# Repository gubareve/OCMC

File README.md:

# Open-source Custom Mechanical Keyboard

OCMC is a custom PCB running on the ATMEGA328P chipset.
Designed using KiCAD 6.0 and assembled using JLCPCB.

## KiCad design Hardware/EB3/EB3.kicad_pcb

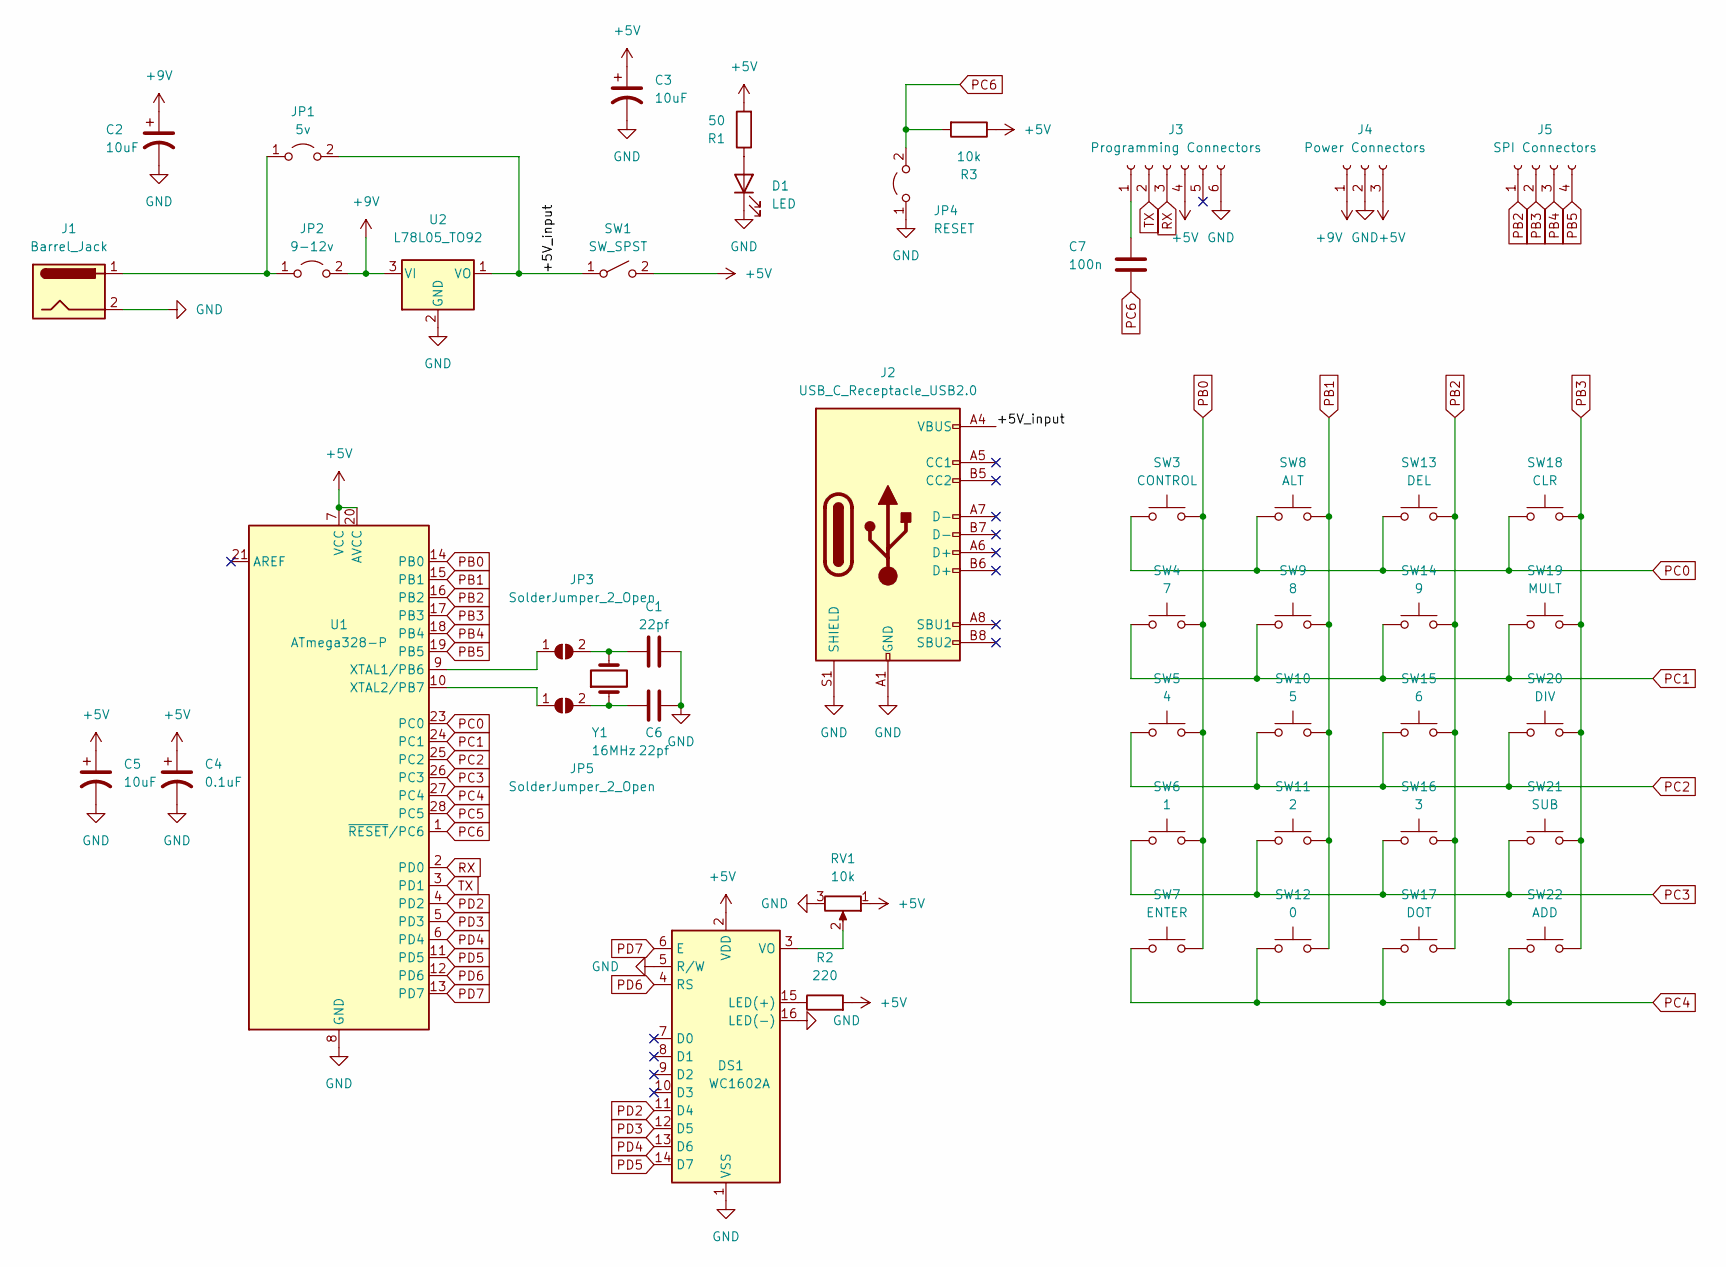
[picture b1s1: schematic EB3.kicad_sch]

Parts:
C1, C6: 22pf; C_0805_2012Metric; LCSC C1804
C2, C3, C5: 10uF; C_0805_2012Metric; LCSC C17024
C4: 0.1uF; C_0805_2012Metric; LCSC C49678
C7: 100n; C_0805_2012Metric; LCSC C49678
D1: LED; LED_0805_2012Metric; LCSC C84256
DS1: WC1602A
J1: Barrel_Jack; BarrelJack_GCT_DCJ200-10-A_Horizontal
J2: USB_C_Receptacle_USB2.0
J3: Programming Connectors; PinSocket_1x06_P2.54mm_Vertical
J4: Power Connectors; PinSocket_1x03_P2.54mm_Vertical
J5: SPI Connectors; PinSocket_1x04_P2.54mm_Vertical
JP1: 5v; TestPoint_2Pads_Pitch2.54mm_Drill0.8mm
JP2: 9-12v; TestPoint_2Pads_Pitch2.54mm_Drill0.8mm
JP3, JP5: SolderJumper_2_Open; SolderJumper-2_P1.3mm_Open_RoundedPad1.0x1.5mm
JP4: RESET; TestPoint_2Pads_Pitch2.54mm_Drill0.8mm
R1: 50; R_0805_2012Metric; LCSC C23182
R2: 220; R_0805_2012Metric; LCSC C17520
R3: 10k; R_0805_2012Metric; LCSC C17414
RV1: 10k; Potentiometer_Piher_PT-6-V_Vertical_Hole
SW1: SW_SPST; SW_Push_2P2T_Toggle_CK_PVA2OAH5xxxxxxV2
SW3: CONTROL; SW_Cherry_MX_Plate_1.00u
SW4: 7; SW_Cherry_MX_Plate_1.00u
SW5: 4; SW_Cherry_MX_Plate_1.00u
SW6: 1; SW_Cherry_MX_Plate_1.00u
SW7: ENTER; SW_Cherry_MX_Plate_1.00u
SW8: ALT; SW_Cherry_MX_Plate_1.00u
SW9: 8; SW_Cherry_MX_Plate_1.00u
SW10: 5; SW_Cherry_MX_Plate_1.00u
SW11: 2; SW_Cherry_MX_Plate_1.00u
SW12: 0; SW_Cherry_MX_Plate_1.00u
SW13: DEL; SW_Cherry_MX_Plate_1.00u
SW14: 9; SW_Cherry_MX_Plate_1.00u
SW15: 6; SW_Cherry_MX_Plate_1.00u
SW16: 3; SW_Cherry_MX_Plate_1.00u
SW17: DOT; SW_Cherry_MX_Plate_1.00u
SW18: CLR; SW_Cherry_MX_Plate_1.00u
SW19: MULT; SW_Cherry_MX_Plate_1.00u
SW20: DIV; SW_Cherry_MX_Plate_1.00u
SW21: SUB; SW_Cherry_MX_Plate_1.00u
SW22: ADD; SW_Cherry_MX_Plate_1.00u
U1: ATmega328-P; DIP-28_W7.62mm
U2: L78L05_TO92; TO-92_Inline
Y1: 16MHz; Crystal_SMD_3225-4Pin_3.2x2.5mm; LCSC C13738

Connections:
+5V: C3.1, C4.1, C5.1, DS1.2 (VDD), J3.4, J4.3, R1.2, R2.2, R3.1, RV1.1, SW1.2 (B), U1.7 (VCC), U1.20 (AVCC)
+9V: C2.1, J4.1, JP2.2 (B), U2.3 (VI)
/+5V_input: J2.A4 (VBUS), J2.A9 (VBUS), J2.B4 (VBUS), J2.B9 (VBUS), JP1.2 (B), SW1.1 (A), U2.1 (VO)
GND: C1.2, C2.2, C3.2, C4.2, C5.2, C6.2, D1.1 (K), DS1.1 (VSS), DS1.5 (R/W), DS1.16 (LED(-)), J1.2, J2.A1 (GND), J2.A12 (GND), J2.B1 (GND), J2.B12 (GND), J2.S1 (SHIELD), J3.6, J4.2, JP4.1 (A), RV1.3, U1.8 (GND), U1.22 (GND), U2.2 (GND), Y1.3
unnamed: C1.1, JP3.2 (B), Y1.2
unnamed: C6.1, JP5.2 (B), Y1.1
unnamed: C7.1, J3.1
unnamed: D1.2 (A), R1.1
unnamed: DS1.3 (VO), RV1.2
unnamed: DS1.15 (LED(+)), R2.1
unnamed: J1.1, JP1.1 (A), JP2.1 (A)
unnamed: JP3.1 (A), U1.9 (XTAL1/PB6)
unnamed: JP5.1 (A), U1.10 (XTAL2/PB7)
PB0: SW3.2, SW4.2, SW5.2, SW6.2, SW7.2, U1.14 (PB0)
PB1: SW8.2, SW9.2, SW10.2, SW11.2, SW12.2, U1.15 (PB1)
PB2: J5.1, SW13.2, SW14.2, SW15.2, SW16.2, SW17.2, U1.16 (PB2)
PB3: J5.2, SW18.2, SW19.2, SW20.2, SW21.2, SW22.2, U1.17 (PB3)
PB4: J5.3, U1.18 (PB4)
PB5: J5.4, U1.19 (PB5)
PC0: SW3.1, SW8.1, SW13.1, SW18.1, U1.23 (PC0)
PC1: SW4.1, SW9.1, SW14.1, SW19.1, U1.24 (PC1)
PC2: SW5.1, SW10.1, SW15.1, SW20.1, U1.25 (PC2)
PC3: SW6.1, SW11.1, SW16.1, SW21.1, U1.26 (PC3)
PC4: SW7.1, SW12.1, SW17.1, SW22.1, U1.27 (PC4)
PC5: U1.28 (PC5)
PC6: C7.2, JP4.2 (B), R3.2, U1.1 (~RESET/PC6)
PD2: DS1.11 (D4), U1.4 (PD2)
PD3: DS1.12 (D5), U1.5 (PD3)
PD4: DS1.13 (D6), U1.6 (PD4)
PD5: DS1.14 (D7), U1.11 (PD5)
PD6: DS1.4 (RS), U1.12 (PD6)
PD7: DS1.6 (E), U1.13 (PD7)
RX: J3.3, U1.2 (PD0)
TX: J3.2, U1.3 (PD1)

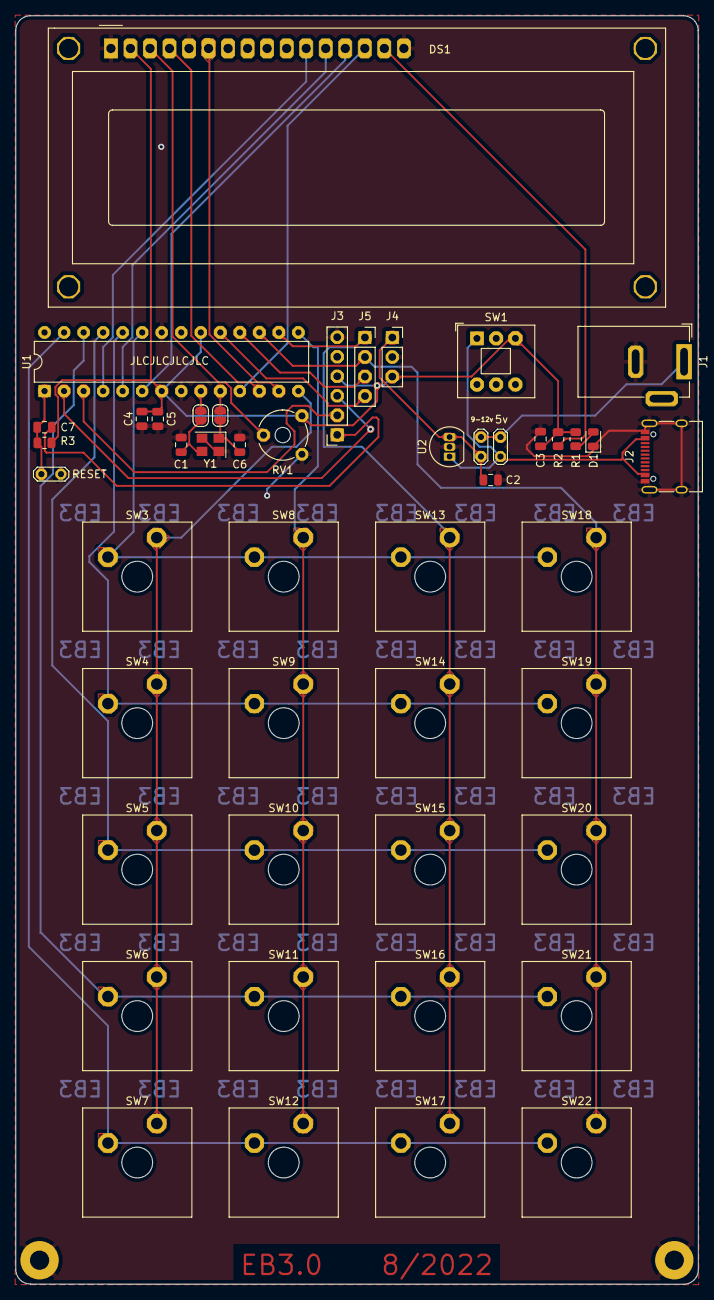
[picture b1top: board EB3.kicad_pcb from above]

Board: 2 copper layers, 88.8 x 165.0 mm, 47 parts (0 on the bottom side), 33 nets.

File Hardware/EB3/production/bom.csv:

Designator,Footprint,Quantity,Value,LCSC Part #
J2,USB_C_Receptacle_XKB_U262-16XN-4BVC11,1,USB_C_Receptacle,
Y1,Crystal_SMD_3225-4Pin_3.2x2.5mm,1,16MHz,C13738
D1,LED_0805_2012Metric,1,LED,C84256
C5,C_0805_2012Metric,1,10uF,C17024
JP3,SolderJumper-2_P1.3mm_Open_RoundedPad1.0x1.5mm,1,SolderJumper_2_Open,
J4,PinSocket_1x03_P2.54mm_Vertical,1,Power Connectors,
J3,PinSocket_1x06_P2.54mm_Vertical,1,Programming Connectors,
C2,C_0805_2012Metric,1,10uF,C17024
DS1,WC1602A,1,WC1602A,
SW3,SW_Cherry_MX_Plate_1.00u,1,CONTROL,
SW15,SW_Cherry_MX_Plate_1.00u,1,6,
SW9,SW_Cherry_MX_Plate_1.00u,1,8,
SW5,SW_Cherry_MX_Plate_1.00u,1,4,
U1,DIP-28_W7.62mm,1,ATmega328-P,
JP5,SolderJumper-2_P1.3mm_Open_RoundedPad1.0x1.5mm,1,SolderJumper_2_Open,
RV1,Potentiometer_Piher_PT-6-V_Vertical_Hole,1,10k,
R3,R_0805_2012Metric,1,10k,C17414
SW10,SW_Cherry_MX_Plate_1.00u,1,5,
SW7,SW_Cherry_MX_Plate_1.00u,1,ENTER,
C3,C_0805_2012Metric,1,10uF,C17024
JP2,TestPoint_2Pads_Pitch2.54mm_Drill0.8mm,1,9-12v,
SW12,SW_Cherry_MX_Plate_1.00u,1,0,
SW19,SW_Cherry_MX_Plate_1.00u,1,MULT,
SW13,SW_Cherry_MX_Plate_1.00u,1,DEL,
JP4,TestPoint_2Pads_Pitch2.54mm_Drill0.8mm,1,RESET,
C4,C_0805_2012Metric,1,0.1uF,C49678
SW21,SW_Cherry_MX_Plate_1.00u,1,SUB,
J1,BarrelJack_GCT_DCJ200-10-A_Horizontal,1,Barrel_Jack,
SW20,SW_Cherry_MX_Plate_1.00u,1,DIV,
SW8,SW_Cherry_MX_Plate_1.00u,1,ALT,
C7,C_0805_2012Metric,1,100n,C49678
C6,C_0805_2012Metric,1,22pf,C1804
SW11,SW_Cherry_MX_Plate_1.00u,1,2,
J5,PinSocket_1x04_P2.54mm_Vertical,1,SPI Connectors,
SW16,SW_Cherry_MX_Plate_1.00u,1,3,
C1,C_0805_2012Metric,1,22pf,C1804
SW18,SW_Cherry_MX_Plate_1.00u,1,CLR,
SW4,SW_Cherry_MX_Plate_1.00u,1,7,
SW6,SW_Cherry_MX_Plate_1.00u,1,1,
SW1,SW_Push_2P2T_Toggle_CK_PVA2OAH5xxxxxxV2,1,SW_SPST,
SW22,SW_Cherry_MX_Plate_1.00u,1,ADD,
R1,R_0805_2012Metric,1,50,
SW17,SW_Cherry_MX_Plate_1.00u,1,DOT,
U2,TO-92_Inline,1,L78L05_TO92,
SW14,SW_Cherry_MX_Plate_1.00u,1,9,
JP1,TestPoint_2Pads_Pitch2.54mm_Drill0.8mm,1,5v,
R2,R_0805_2012Metric,1,220,C17520

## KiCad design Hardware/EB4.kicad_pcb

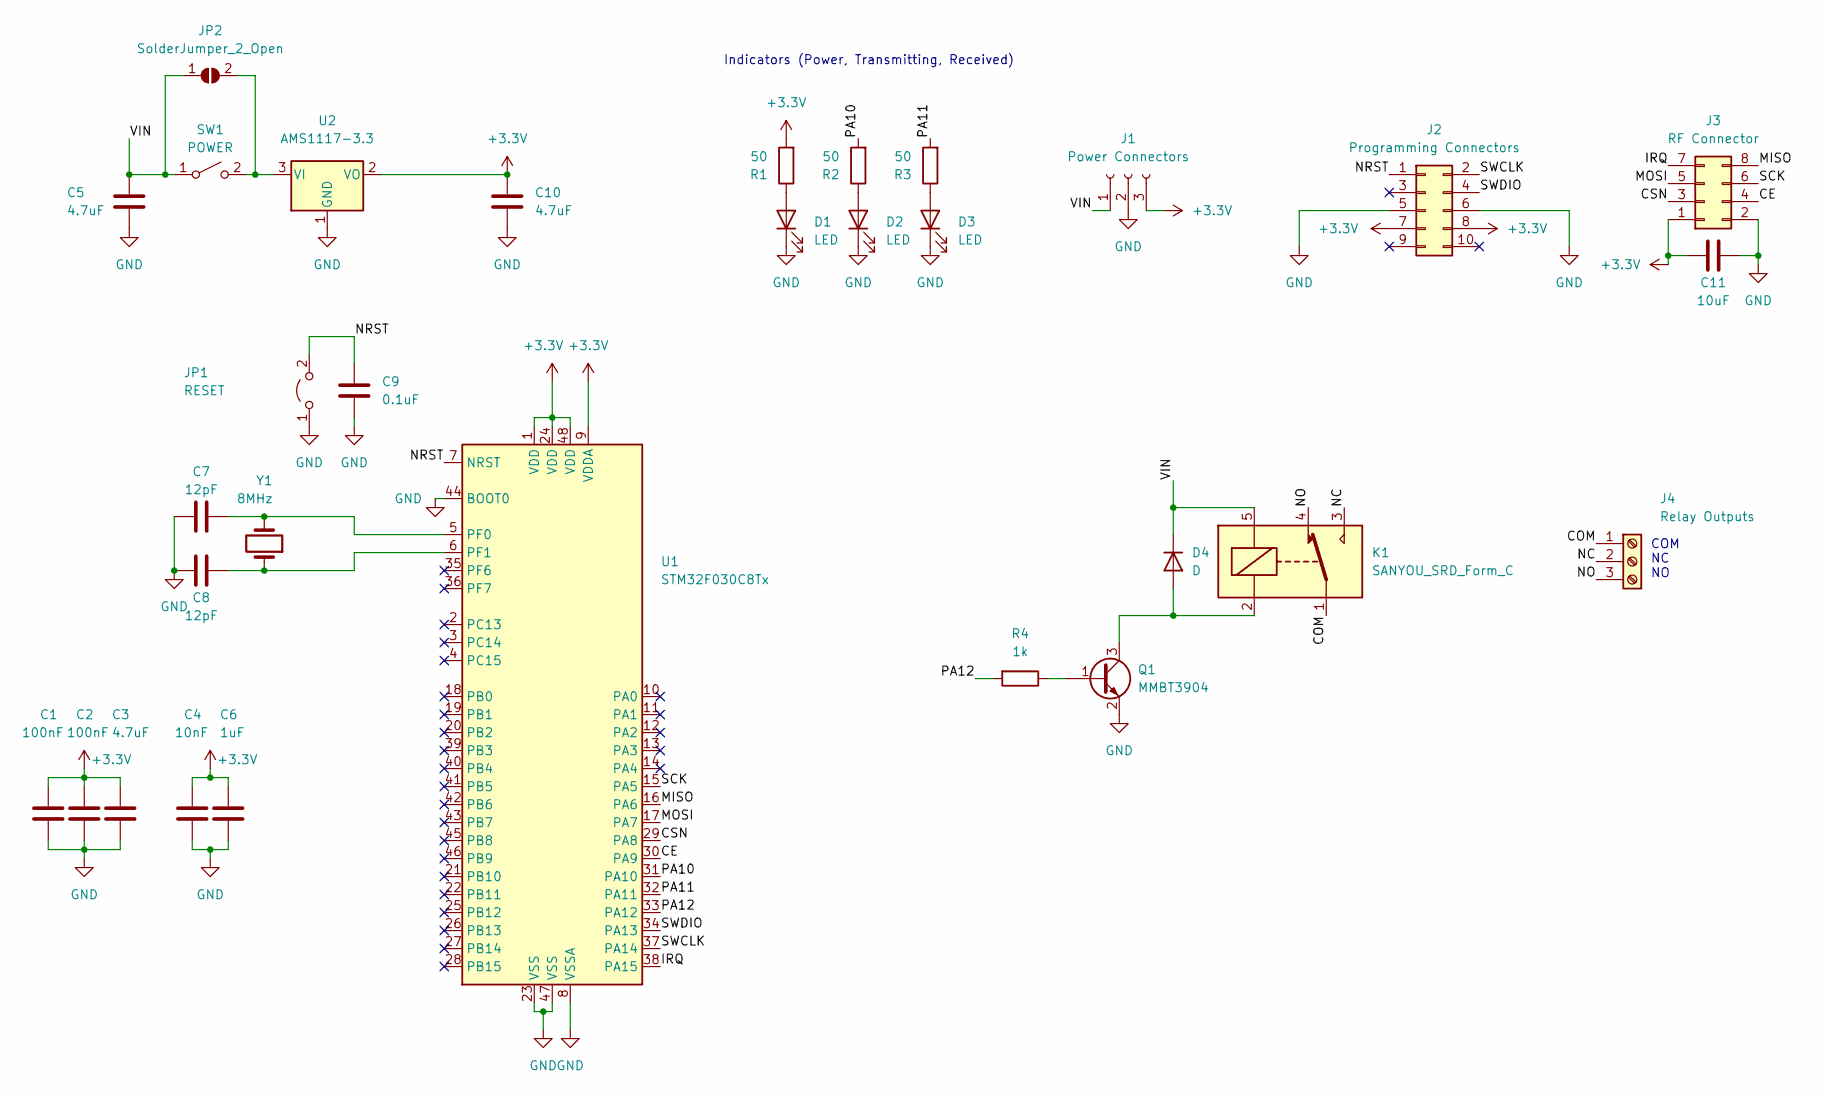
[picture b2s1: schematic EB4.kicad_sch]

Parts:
C1, C2: 100nF; C_0402_1005Metric; LCSC C1525
C3, C5, C10: 4.7uF; C_0402_1005Metric; LCSC C23733
C4: 10nF; C_0402_1005Metric; LCSC C15195
C6: 1uF; C_0402_1005Metric; LCSC C52923
C7, C8: 12pF; C_0402_1005Metric; LCSC C1547
C9: 0.1uF; C_0402_1005Metric; LCSC C1525
C11: 10uF; C_0603_1608Metric; LCSC C19702
D1, D2, D3: LED; LED_0805_2012Metric; LCSC C84256
D4: D; D_SOD-323; LCSC C191023
J1: Power Connectors; PinSocket_1x03_P2.54mm_Vertical
J2: Programming Connectors; PinSocket_2x05_P2.54mm_Vertical
J3: RF Connector; PinSocket_2x04_P2.54mm_Vertical
J4: Relay Outputs; PinSocket_1x03_P2.54mm_Vertical
JP1: RESET; TestPoint_2Pads_Pitch2.54mm_Drill0.8mm
JP2: SolderJumper_2_Open; SolderJumper-2_P1.3mm_Open_TrianglePad1.0x1.5mm
K1: SANYOU_SRD_Form_C; Relay_SPDT_SANYOU_SRD_Series_Form_C
Q1: MMBT3904; SOT-23; LCSC C20526
R1, R2, R3: 50; R_0402_1005Metric; LCSC C25125
R4: 1k; R_0402_1005Metric; LCSC C11702
SW1: POWER; SW_Push_1P1T_NO_CK_KSC6xxJ; LCSC C318884
U1: STM32F030C8Tx; LQFP-48_7x7mm_P0.5mm; LCSC C23922
U2: AMS1117-3.3; SOT-223-3_TabPin2; LCSC C6186
Y1: 8MHz; Crystal_SMD_HC49-SD; LCSC C12674

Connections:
+3.3V: C1.1, C2.1, C3.1, C4.1, C6.1, C10.1, C11.2, J1.3, J2.7, J2.8, J3.1, R1.2, U1.1 (VDD), U1.9 (VDDA), U1.24 (VDD), U1.48 (VDD), U2.2 (VO)
/CE: J3.4, U1.30 (PA9)
/COM: J4.1, K1.1
/CSN: J3.3, U1.29 (PA8)
/IRQ: J3.7, U1.38 (PA15)
/MISO: J3.8, U1.16 (PA6)
/MOSI: J3.5, U1.17 (PA7)
/NC: J4.2, K1.3
/NO: J4.3, K1.4
/NRST: C9.1, J2.1, JP1.2 (B), U1.7 (NRST)
/PA10: R2.2, U1.31 (PA10)
/PA11: R3.2, U1.32 (PA11)
/PA12: R4.2, U1.33 (PA12)
/SCK: J3.6, U1.15 (PA5)
/SWCLK: J2.2, U1.37 (PA14)
/SWDIO: J2.4, U1.34 (PA13)
/VIN: C5.1, D4.1 (K), J1.1, JP2.1 (A), K1.5, SW1.1 (A)
GND: C1.2, C2.2, C3.2, C4.2, C5.2, C6.2, C7.2, C8.2, C9.2, C10.2, C11.1, D1.1 (K), D2.1 (K), D3.1 (K), J1.2, J2.5, J2.6, J3.2, JP1.1 (A), Q1.2 (E), U1.8 (VSSA), U1.23 (VSS), U1.44 (BOOT0), U1.47 (VSS), U2.1 (GND)
unnamed: C7.1, U1.5 (PF0), Y1.2
unnamed: C8.1, U1.6 (PF1), Y1.1
unnamed: D1.2 (A), R1.1
unnamed: D2.2 (A), R2.1
unnamed: D3.2 (A), R3.1
unnamed: D4.2 (A), K1.2, Q1.3 (C)
unnamed: JP2.2 (B), SW1.2 (B), U2.3 (VI)
unnamed: Q1.1 (B), R4.1

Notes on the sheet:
COM NC NO
Indicators (Power, Transmitting, Received)

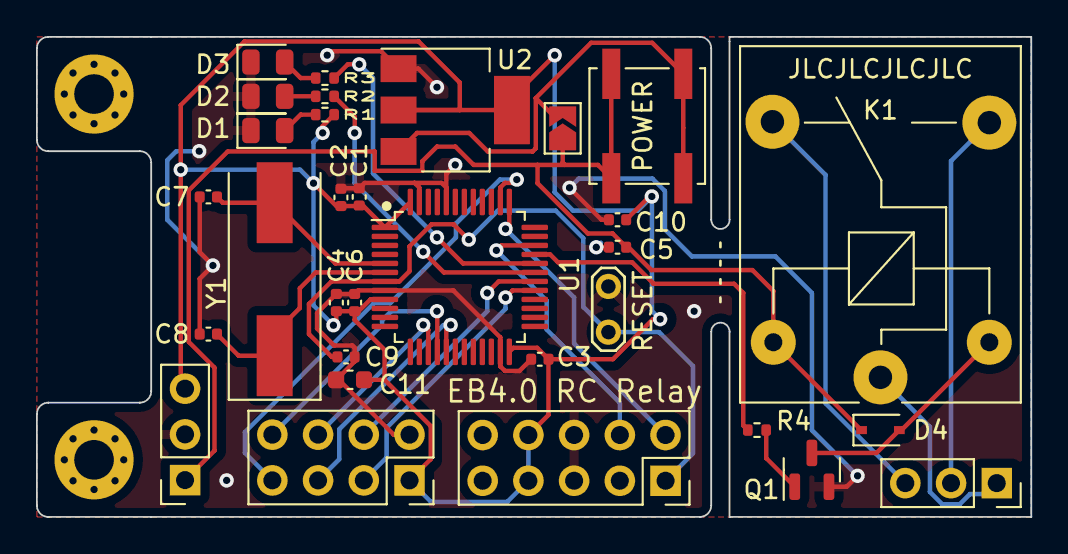
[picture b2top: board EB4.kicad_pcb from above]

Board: 2 copper layers, 55.2 x 26.7 mm, 31 parts (0 on the bottom side), 26 nets.

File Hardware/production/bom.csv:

Designator,Footprint,Quantity,Value,LCSC Part #
D4,D_SOD-323,1,D,C191023
D2,LED_0805_2012Metric,1,LED,C84256
J1,PinSocket_1x03_P2.54mm_Vertical,1,Power Connectors,
C6,C_0402_1005Metric,1,1uF,C52923
U1,LQFP-48_7x7mm_P0.5mm,1,STM32F030C8Tx,C23922
C2,C_0402_1005Metric,1,100nF,C1525
R1,R_0402_1005Metric,1,50,C25125
C10,C_0402_1005Metric,1,4.7uF,C23733
Q1,SOT-23,1,MMBT3904,C20526
C7,C_0402_1005Metric,1,12pF,C1547
C9,C_0402_1005Metric,1,0.1uF,C1525
C8,C_0402_1005Metric,1,12pF,C1547
JP2,SolderJumper-2_P1.3mm_Open_TrianglePad1.0x1.5mm,1,SolderJumper_2_Open,
J2,PinSocket_2x05_P2.54mm_Vertical,1,Programming Connectors,
K1,Relay_SPDT_SANYOU_SRD_Series_Form_C,1,SANYOU_SRD_Form_C,
R4,R_0402_1005Metric,1,1k,C11702
C3,C_0402_1005Metric,1,4.7uF,C23733
C1,C_0402_1005Metric,1,100nF,C1525
D3,LED_0805_2012Metric,1,LED,C84256
R2,R_0402_1005Metric,1,50,C25125
J3,PinSocket_2x04_P2.54mm_Vertical,1,RF Connector,
C4,C_0402_1005Metric,1,10nF,C15195
SW1,SW_Push_1P1T_NO_CK_KSC6xxJ,1,POWER,C318884
J4,PinSocket_1x03_P2.54mm_Vertical,1,Relay Outputs,
JP1,TestPoint_2Pads_Pitch2.54mm_Drill0.8mm,1,RESET,
C5,C_0402_1005Metric,1,4.7uF,C23733
R3,R_0402_1005Metric,1,50,C25125
D1,LED_0805_2012Metric,1,LED,C84256
U2,SOT-223-3_TabPin2,1,AMS1117-3.3,C6186
C11,C_0603_1608Metric,1,10uF,C19702
Y1,Crystal_SMD_HC49-SD,1,8MHz,C12674

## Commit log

2022-10-19 Create LICENSE
2022-10-19 add image of calc
2022-10-19 Add KiCAD project
